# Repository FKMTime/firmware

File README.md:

# FKMTime firmware

## Main Pinout

| #   | IO#   | ADC/STRAP/USB | USAGE          | Notes                  |
|-----|-------|---------------|----------------|------------------------|
| 0   | IO4   | ADC           | SPI SCK        |                        |
| 1   | IO5   | ADC           | SPI MISO       |                        |
| 2   | IO6   |               | SPI MOSI       |                        |
| 3   | IO7   |               |                |                        |
| 4   | IO8   | STRAP         |                |                        |
| 5   | IO9   | STRAP / IPU   |                | INTERNAL PULLUP (10kOhm) |
| 6   | IO10  |               | SHIFTER DATA   |                        |
| 7   | RXD/IO20|             | JACK INPUT     |                        |
| 8   | TXD/IO21|             | SHIFTER CLK    |                        |
| 9   | IO18  | USB           | USB D-         |                        |
| 10  | IO19  | USB           | USB D+         |                        |
| 11  | IO3   | ADC           | BUTTON INPUT   |                        |
| 12  | IO2   | ADC / STRAP   | BATTERY INPUT  |                        |
| 13  | IO1   | ADC           | SHIFTER LATCH  |                        |
| 14  | IO0   | ADC           |                |                        |

**Notes:**
* **STRAP:** Strapping pin
* **IPU:** Internal Pull-up (10kOhm).
* **USB:** Pins used for USB communication.

## Shifters Configuration

| SHIFTER # | USAGE          | BIT1    | BIT2    | BIT3    | BIT4    | BIT5    | BIT6    | BIT7    | BIT8    |
|-----------|----------------|---------|---------|---------|---------|---------|---------|---------|---------|
| 0         | BUTTONS MATRIX | BTN1    | BTN2    | BTN3    | BTN4    |         |         |         |         |
| 1         | LCD 16x2       | SPI_CS  | BL      | RS      | E       | D7      | D6      | D5      | D4      |
| 2         | DISPLAY DIGIT1 | TODO    | TODO    | TODO    | TODO    | TODO    | TODO    | TODO    | TODO    |
| 3         | DISPLAY DIGIT2 | TODO    | TODO    | TODO    | TODO    | TODO    | TODO    | TODO    | TODO    |
| 4         | DISPLAY DIGIT3 | TODO    | TODO    | TODO    | TODO    | TODO    | TODO    | TODO    | TODO    |
| 5         | DISPLAY DIGIT4 | TODO    | TODO    | TODO    | TODO    | TODO    | TODO    | TODO    | TODO    |
| 6         | DISPLAY DIGIT5 | TODO    | TODO    | TODO    | TODO    | TODO    | TODO    | TODO    | TODO    |
| 7         | DISPLAY DIGIT6 | TODO    | TODO    | TODO    | TODO    | TODO    | TODO    | TODO    | TODO    |

## PCB
Pcb files are available as easyeda pro project.
File `FKM3.epro`

## 3D design 
You can view it and/or export it on onshape: 
 - [v1](https://cad.onshape.com/documents/a197fb44982d02cf4b905a34/w/d4d582c400841c8d2afd5356/e/063a9ed468737fb6f67b27f0?renderMode=0&uiState=65d2904a62856512eae60b89)
 - [v2](https://cad.onshape.com/documents/b9e6ecc4d8625f5993c3f9f8/w/500dd0485ca5c8c194e3d3fd/e/a40639e650796ab94408e0d7?renderMode=0&uiState=66239c4fa9b8ad7b949dae01)

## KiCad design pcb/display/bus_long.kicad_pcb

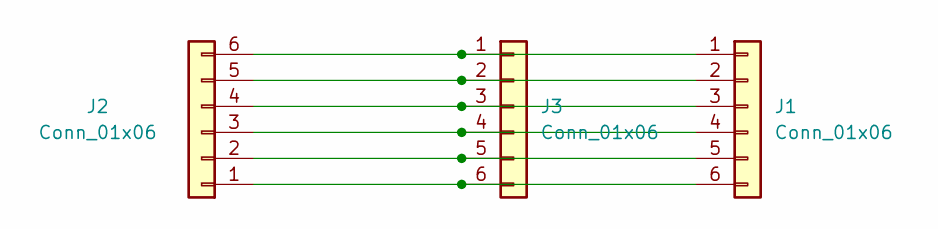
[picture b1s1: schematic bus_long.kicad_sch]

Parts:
J1, J2, J3: Conn_01x06; PinHeader_1x06_P2.54mm_Vertical

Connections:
unnamed: J1.1, J2.6, J3.1
unnamed: J1.2, J2.5, J3.2
unnamed: J1.3, J2.4, J3.3
unnamed: J1.4, J2.3, J3.4
unnamed: J1.5, J2.2, J3.5
unnamed: J1.6, J2.1, J3.6

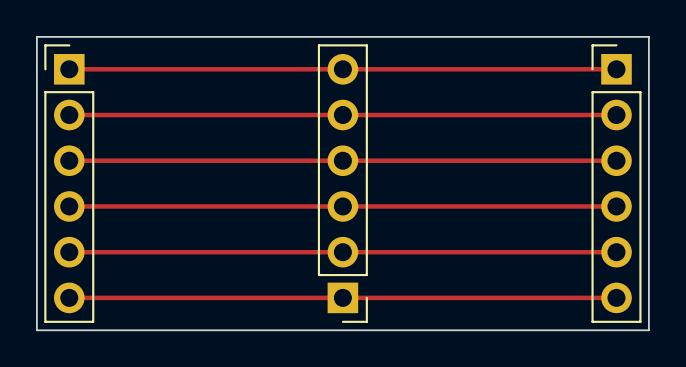
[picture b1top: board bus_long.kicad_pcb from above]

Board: 2 copper layers, 34.0 x 16.3 mm, 3 parts (0 on the bottom side), 6 nets.

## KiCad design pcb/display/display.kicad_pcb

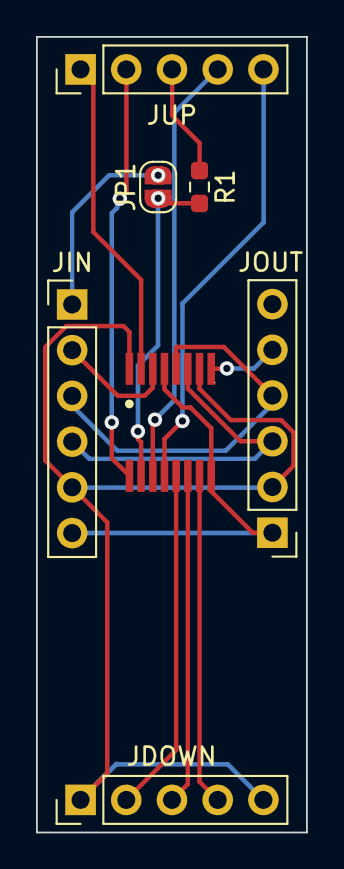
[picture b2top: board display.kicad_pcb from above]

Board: 2 copper layers, 15.0 x 44.2 mm, 7 parts (0 on the bottom side), 16 nets.

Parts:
JDOWN: DOWN; PinHeader_1x05_P2.54mm_Vertical
JIN: INPUT; PinHeader_1x06_P2.54mm_Vertical
JOUT: OUTPUT; PinHeader_1x06_P2.54mm_Vertical
JP1: SolderJumper_2_Open; SolderJumper-2_P1.3mm_Open_RoundedPad1.0x1.5mm
JUP: UP; PinHeader_1x05_P2.54mm_Vertical
R1: R220; R_0603_1608Metric_Pad0.98x0.95mm_HandSolder
U1: 74HC595; TSSOP16

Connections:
8_O: JIN.1, JP1.2 (B)
+5V: JDOWN.1, JDOWN.5, JIN.5, JOUT.2, U1.10 (~SRCLR), U1.16 (VCC)
DS: JIN.2, U1.14 (SER)
DS_O: JOUT.5, U1.9 (QH')
GND: JIN.6, JOUT.1, U1.8 (GND), U1.13 (~OE)
unnamed: JUP.3, R1.1
QA: JUP.1, U1.15 (QA)
QB: JUP.2, U1.1 (QB)
QC: JP1.1 (A), R1.2, U1.2 (QC)
QD: JUP.4, U1.3 (QD)
QE: JUP.5, U1.4 (QE)
QF: JDOWN.2, U1.5 (QF)
QG: JDOWN.3, U1.6 (QG)
QH: JDOWN.4, U1.7 (QH)
SHCP: JIN.4, JOUT.3, U1.11 (SRCLK)
STCP: JIN.3, JOUT.4, U1.12 (RCLK)

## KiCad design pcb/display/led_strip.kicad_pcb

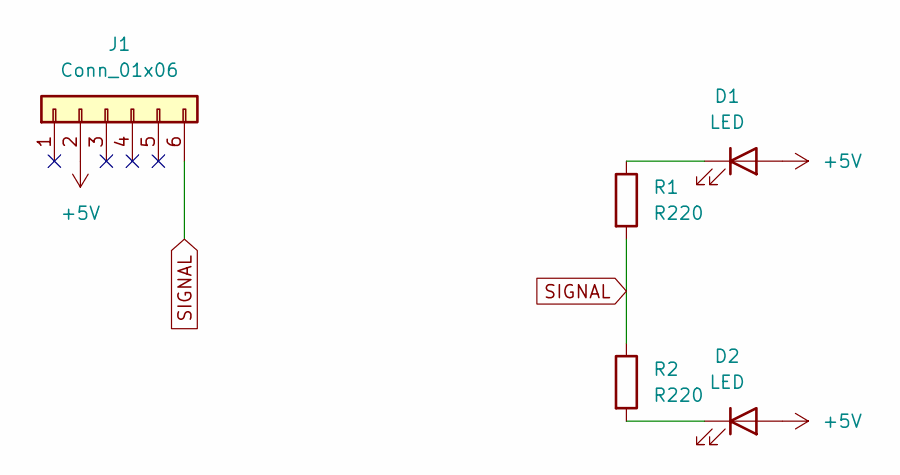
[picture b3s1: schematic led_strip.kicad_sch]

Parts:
D1, D2: LED; LED_D3.0mm
J1: Conn_01x06; PinHeader_1x06_P2.54mm_Vertical
R1, R2: R220; R_0603_1608Metric_Pad0.98x0.95mm_HandSolder

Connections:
+5V: D1.2 (A), D2.2 (A), J1.2
unnamed: D1.1 (K), R1.1
unnamed: D2.1 (K), R2.2
SIGNAL: J1.6, R1.2, R2.1

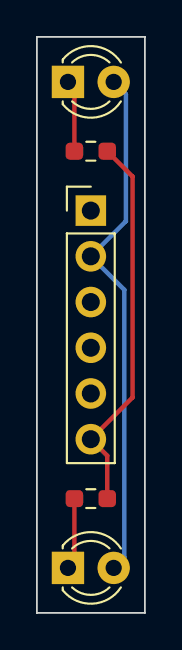
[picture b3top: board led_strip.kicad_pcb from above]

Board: 2 copper layers, 6.0 x 32.0 mm, 5 parts (0 on the bottom side), 4 nets.

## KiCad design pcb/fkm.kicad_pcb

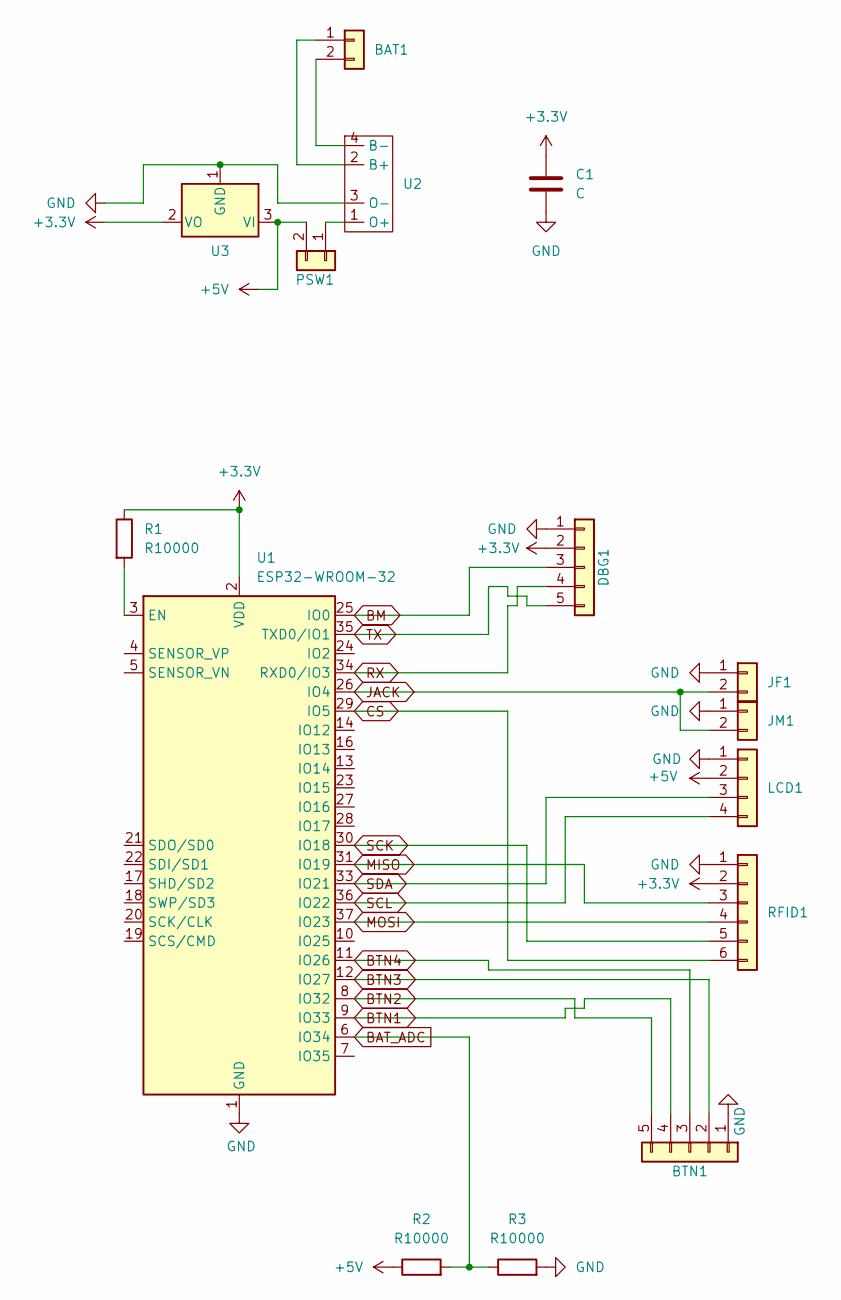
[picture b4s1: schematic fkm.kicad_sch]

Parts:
BAT1: BAT1; PinHeader_1x02_P2.54mm_Vertical
BTN1: Conn_01x05; PinHeader_1x05_P2.54mm_Vertical
C1: C; C_0805_2012Metric_Pad1.18x1.45mm_HandSolder
DBG1: Conn_01x05; PinHeader_1x05_P2.00mm_Vertical
JF1: JACK_FEMALE; PinHeader_1x02_P2.54mm_Vertical
JM1: JACK_MALE; PinHeader_1x02_P2.54mm_Vertical
LCD1: LCD; PinHeader_1x04_P2.54mm_Vertical
PSW1: POWER_SW; PinHeader_1x02_P2.54mm_Vertical
R1, R2, R3: R10000; R_0805_2012Metric_Pad1.20x1.40mm_HandSolder
RFID1: RFID; PinHeader_1x06_P2.54mm_Vertical
U1: ESP32-WROOM-32
U2: 18650; 18650usbc
U3: AMS1117-3.3; SOT-223-3_TabPin2

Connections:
+3.3V: C1.2, DBG1.2, R1.1, RFID1.2, U1.2 (VDD), U3.2 (VO)
+5V: LCD1.2, PSW1.2, R2.1, U3.3 (VI)
BAT_ADC: R2.2, R3.1, U1.6 (IO34)
BM: DBG1.3, U1.25 (IO0)
BTN1: BTN1.4, U1.9 (IO33)
BTN2: BTN1.5, U1.8 (IO32)
BTN3: BTN1.2, U1.12 (IO27)
CS: RFID1.6, U1.29 (IO5)
GND: BTN1.1, C1.1, DBG1.1, JF1.1, JM1.1, LCD1.1, R3.2, RFID1.1, U1.1 (GND), U1.15 (GND), U1.38 (GND), U1.39 (GND), U2.3 (O-), U3.1 (GND)
JACK: JF1.2, JM1.2, U1.26 (IO4)
MISO: RFID1.3, U1.31 (IO19)
MOSI: RFID1.4, U1.37 (IO23)
unnamed: BAT1.1, U2.2 (B+)
unnamed: BAT1.2, U2.4 (B-)
unnamed: BTN1.3, U1.11 (IO26)
unnamed: PSW1.1, U2.1 (O+)
unnamed: R1.2, U1.3 (EN)
RX: DBG1.4, U1.34 (RXD0/IO3)
SCK: RFID1.5, U1.30 (IO18)
SCL: LCD1.4, U1.36 (IO22)
SDA: LCD1.3, U1.33 (IO21)
TX: DBG1.5, U1.35 (TXD0/IO1)

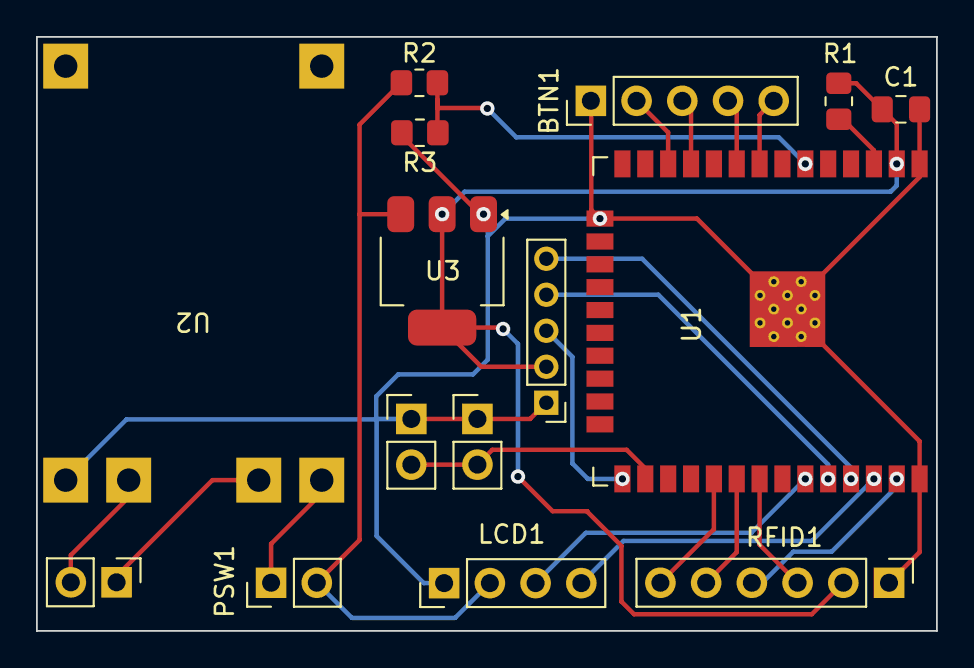
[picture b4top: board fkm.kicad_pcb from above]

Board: 2 copper layers, 50.0 x 33.0 mm, 15 parts (0 on the bottom side), 22 nets.

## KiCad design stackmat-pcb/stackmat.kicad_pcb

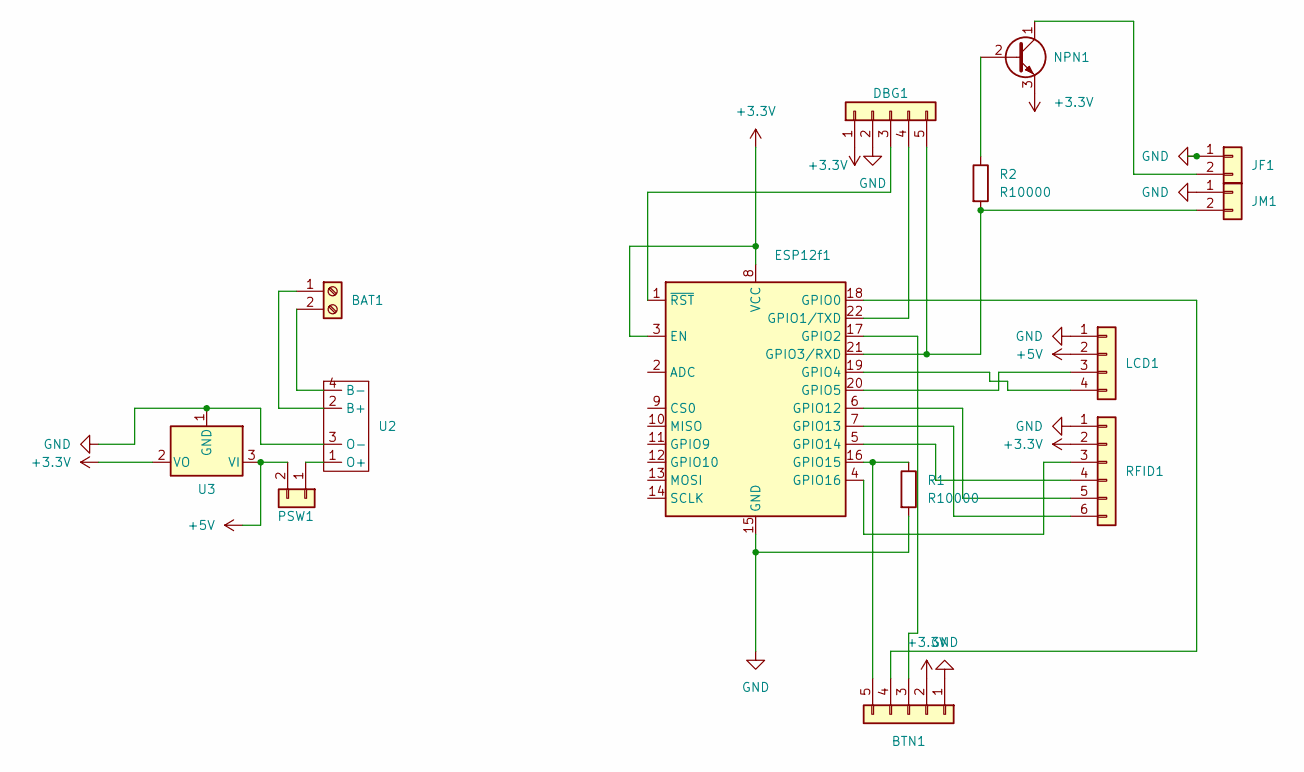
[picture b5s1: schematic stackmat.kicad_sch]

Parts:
BAT1: Screw_Terminal_01x02; TerminalBlock_4Ucon_1x02_P3.50mm_Horizontal
BTN1: Conn_01x05; PinHeader_1x05_P2.54mm_Vertical
DBG1: Conn_01x05; PinHeader_1x05_P2.54mm_Vertical
ESP12f1: ESP-12F/E; ESP-12E
JF1: JACK_FEMALE; PinHeader_1x02_P2.54mm_Vertical
JM1: JACK_MALE; PinHeader_1x02_P2.54mm_Vertical
LCD1: LCD; PinHeader_1x04_P2.54mm_Vertical
NPN1: BC337; TO-92_Inline
PSW1: POWER_SW; PinHeader_1x02_P2.54mm_Vertical
R1, R2: R10000; R_Axial_DIN0204_L3.6mm_D1.6mm_P7.62mm_Horizontal
RFID1: RFID; PinHeader_1x06_P2.54mm_Vertical
U2: 18650; 18650usbc
U3: AMS1117-3.3; SOT-223-3_TabPin2

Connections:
+3.3V: BTN1.2, DBG1.1, ESP12f1.3 (EN), ESP12f1.8 (VCC), NPN1.3 (E), RFID1.2, U3.2 (VO)
+5V: LCD1.2, PSW1.2, U3.3 (VI)
GND: BTN1.1, DBG1.2, ESP12f1.15 (GND), JF1.1, JM1.1, LCD1.1, R1.2, RFID1.1, U2.3 (O-), U3.1 (GND)
unnamed: BAT1.1, U2.2 (B+)
unnamed: BAT1.2, U2.4 (B-)
unnamed: BTN1.3, ESP12f1.17 (GPIO2)
unnamed: BTN1.4, ESP12f1.18 (GPIO0)
unnamed: BTN1.5, ESP12f1.16 (GPIO15), R1.1
unnamed: DBG1.3, ESP12f1.1 (~RST)
unnamed: DBG1.4, ESP12f1.22 (GPIO1/TXD)
unnamed: DBG1.5, ESP12f1.21 (GPIO3/RXD), JM1.2, R2.2
unnamed: ESP12f1.19 (GPIO4), LCD1.4
unnamed: ESP12f1.20 (GPIO5), LCD1.3
unnamed: ESP12f1.6 (GPIO12), RFID1.5
unnamed: ESP12f1.7 (GPIO13), RFID1.6
unnamed: ESP12f1.5 (GPIO14), RFID1.4
unnamed: ESP12f1.4 (GPIO16), RFID1.3
unnamed: JF1.2, NPN1.1 (C)
unnamed: NPN1.2 (B), R2.1
unnamed: PSW1.1, U2.1 (O+)

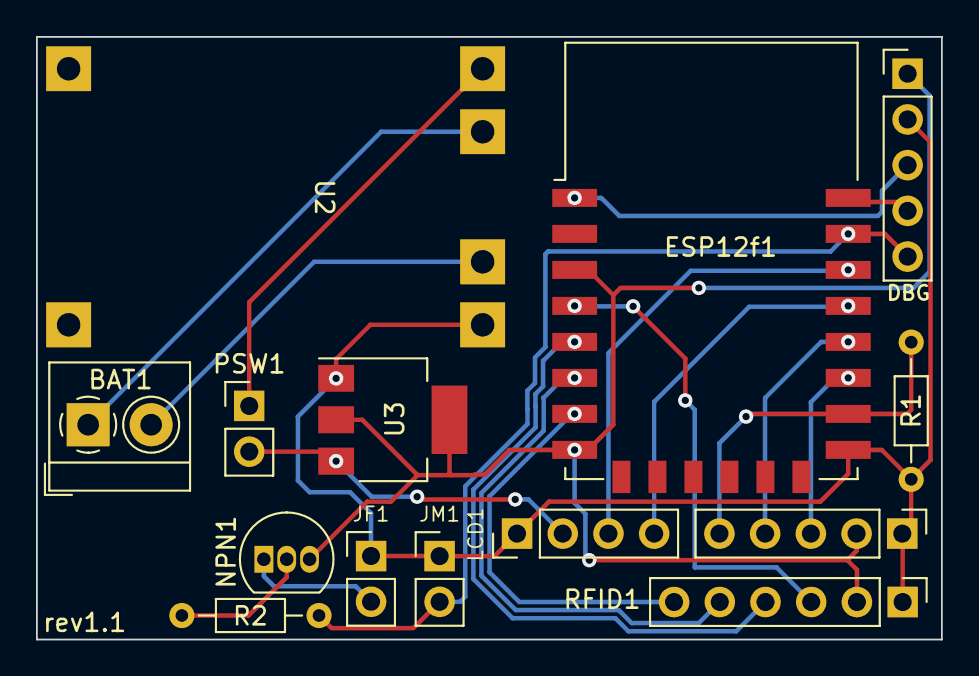
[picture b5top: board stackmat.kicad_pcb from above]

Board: 2 copper layers, 50.3 x 33.5 mm, 14 parts (0 on the bottom side), 20 nets.

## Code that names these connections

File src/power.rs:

//! Sleep state machine: Awake → Sleeping (radio off) → DeepSleep (chip off, button wakes it).
//!
//! Display/input code only calls [`request_sleep`] / [`wake`] / [`enter_deep_sleep`];
//! [`Supervisor::tick`] (main loop) does the radio, websocket and BLE side of each transition.

use embassy_sync::{blocking_mutex::raw::CriticalSectionRawMutex, signal::Signal};
use embassy_time::{Duration, Instant};
use esp_hal_wifimanager::WifiManager;
use portable_atomic::{AtomicBool, Ordering};

pub type SleepSignal = Signal<CriticalSectionRawMutex, bool>;

/// Time between the websocket close frame and the radio going off; also debounces quick wakes.
const SLEEP_SETTLE: Duration = Duration::from_secs(15);

static SLEEPING: AtomicBool = AtomicBool::new(false);
/// v3 only: the cpu runs at 10 MHz until the next reset.
static DEEPER: AtomicBool = AtomicBool::new(false);

pub fn is_sleeping() -> bool {
    SLEEPING.load(Ordering::Relaxed)
}

#[cfg_attr(not(feature = "v3"), allow(dead_code))]
pub fn is_deeper_sleeping() -> bool {
    DEEPER.load(Ordering::Relaxed)
}

pub fn request_sleep() {
    SLEEPING.store(true, Ordering::Relaxed);
}

pub fn wake() {
    SLEEPING.store(false, Ordering::Relaxed);
}

/// Powers the chip down until one of the four buttons is pressed (wake = reset).
#[cfg(feature = "v4")]
pub fn enter_deep_sleep() -> ! {
    use esp_hal::gpio::{Event, Input, InputConfig, Pin, Pull, WakeupConfig};
    use esp_hal::rtc_cntl::sleep::{LowPower, RtcSleepConfig};

    // SAFETY: called right before deep sleep, after which nothing else uses these pins.
    let (pins, lpwr) = unsafe {
        (
            [
                esp_hal::peripherals::GPIO0::steal().degrade(),
                esp_hal::peripherals::GPIO1::steal().degrade(),
                esp_hal::peripherals::GPIO2::steal().degrade(),
                esp_hal::peripherals::GPIO3::steal().degrade(),
            ],
            esp_hal::peripherals::LPWR::steal(),
        )
    };

    // pull-down like the old RtcioWakeupSource did for a high-level wake
    let input_config = InputConfig::default().with_pull(Pull::Down);
    let wakeup_config = WakeupConfig::default().with_low_power_path(true);
    let mut wakeup_pins = pins.map(|pin| Input::new(pin, input_config));
    for pin in &mut wakeup_pins {
        if let Err(e) = pin.apply_wakeup_config(&wakeup_config) {
            log::error!("Wakeup pin config failed: {e:?}");
        }
        pin.listen(Event::HighLevel);
    }

    LowPower::new(lpwr).sleep_deep(RtcSleepConfig::deep())
}

/// v3 has no wakeable deep sleep: the cpu clock drops to 10 MHz until the next reset.
#[cfg(feature = "v3")]
pub fn enter_deep_sleep() {
    crate::utils::deeper_sleep();
    DEEPER.store(true, Ordering::Relaxed);
}

/// Applies sleep transitions to the radio, websocket and BLE tasks.
pub struct Supervisor<'a> {
    wifi: &'a WifiManager,
    sleeping: bool,
    /// Set while waiting [`SLEEP_SETTLE`] before turning the radio off.
    settling_since: Option<Instant>,
}

impl<'a> Supervisor<'a> {
    pub fn new(wifi: &'a WifiManager) -> Self {
        Self {
            wifi,
            sleeping: false,
            settling_since: None,
        }
    }

    /// Call periodically (never blocks for long).
    pub fn tick(&mut self) {
        let sleeping = is_sleeping();

        if let Some(since) = self.settling_since {
            if !sleeping {
                // woken while settling: reset the ws state, the next tick restarts everything
                self.settling_since = None;
                crate::ws::SLEEP.signal(true);
            } else if since.elapsed() >= SLEEP_SETTLE {
                self.settling_since = None;
                crate::ws::SLEEP.signal(true);
                self.wifi.stop_radio();
            }
            return;
        }

        if sleeping == self.sleeping {
            return;
        }

        self.sleeping = sleeping;
        crate::bluetooth::SLEEP.signal(sleeping);
        if sleeping {
            log::warn!("Entering sleep mode!");
            crate::ws::close(4000, "Going into sleep mode");
            self.settling_since = Some(Instant::now());
        } else {
            crate::ws::SLEEP.signal(false);
            self.wifi.restart_radio();
        }
    }
}

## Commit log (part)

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2025-03-13 feat: qa tests
2025-03-13 feat: add wifi setup to qa tests
2025-03-23 chore: update dependencies
2025-03-28 feat: do not use nvs if in qa
2025-03-29 chore: print firmware/version/revision on startup
2025-03-29 feat: add Auto Server Discovery checkbox to wifi panel
2025-03-31 chore: print button presses on qa mode
2025-04-05 fix: speed up cpu clock
2025-04-05 fix: multiple things
2025-04-06 chore: sleep feature (to enable/disable sleep)
2025-04-06 feat: use ag-lcd fork with async support fix: decrease button debounce time fix: ms time to str above 9 minutes 59seconds
2025-04-08 chore: print card skip warn msg
2025-04-08 fix: do not try to send frame if its too big
2025-04-08 feat: frame splitting
2025-04-09 feat: check heap space on log
2025-04-10 chore: mkdir /tmp/fkm-build in release script
2025-04-13 chore: new version of easyeda pcb proj
2025-04-15 explore: esp-now communication
2025-05-15 fix: clippy warnings
2025-05-15 fix: uart slowdown issue (closes #21 #22)
2025-05-15 fix: release build const
2025-05-29 chore: update dependencies (so it will build)
2025-05-29 fix: clippy error
2025-05-29 docs: add pinout map to readme
2025-06-03 chore: update to newer version of esp-hal
2025-06-03 fix: fmt
2025-06-24 feat: use async interface for battery adc readings (esp32c3 only)
2025-06-25 chore: remove esp32 generic port with cleanup
2025-06-25 fix: build/clippy ci with removed `esp32c3` feature
2025-06-25 fix: actually fix ci
2025-07-16 chore: update to newest esp-hal
2025-07-16 fix: fmt issues
2025-07-17 chore: use reeleased version of esp-hal-wifimanager (finally!)
2025-07-18 feat: better startup screen
2025-08-07 feat: update pcb proj
2025-08-17 chore: update mfrc crate
2025-09-09 chore: dependencies bump
2025-09-22 feat: auto add device feature fix: show proper ws_rw errors
2025-09-23 fix: typo
2025-09-24 feat: generate sign key
2025-09-24 feat: packet signing
2025-09-25 explore: check secured read from rfid card [skip ci]
2025-09-25 fix: invalidate SIGN_KEY on reset wifi
2025-09-26 fix: self signed rsa certs
2025-09-27 feat: server trust
2025-09-27 explore: test rfid read/write secured
2025-09-28 fix: tls read select cancel
2025-09-28 feat: recv fkm_token from device settings
2025-10-01 feat: secured rfid check
2025-10-03 fix: return from ws_rw loop on error (closes #25)
2025-10-03 feat: only update when server is trusted
2025-10-06 explore: disable usb after wifi connection
2025-10-11 fix: do not print token in the info log (use debug)
2025-10-12 wip: bluetooth connection to the own displays
2025-10-13 chore: update esp-hal version
2025-10-14 fix: update wifimanager to fix "sticky" ble
2025-10-14 wip: config menu
2025-10-14 wip: signing and unsigning cards
2025-10-14 wip: card signing UI
2025-10-15 wip: try to connect to fkm display example [skip ci]
2025-10-15 explore: send bt data constantly [skip ci]
2025-10-15 explore: detect disconnect from peer [skip ci]
2025-10-16 wip: messy ble display re-bonding [skip ci]
2025-10-17 wip: better menu scene management [skip ci]
2025-10-18 wip: ble displays menu [skip ci]
2025-10-18 wip: connect to ble from menu [skip ci]
2025-10-19 feat: better ble display connection management
2025-10-19 fix: ble connection
2025-10-19 chore: make ble signalling cleaner
2025-10-20 chore: more error handling (no unwraps, only expects in codepath's that cannot fail)
2025-10-20 chore: even less expect's
2025-10-21 feat: only allow cards signing/unsigning when auto setup enabled
2025-10-23 feat: ble display sleep
2025-10-30 feat: show server not trusted error after connection
2025-10-30 chore: expect is no more
2025-10-31 chore: update to stable version of esp-hal
2025-10-31 chore: remove old esp-now experiment
2025-11-01 fix: lcd hanging on start (fucking wifi is blocking - not my issue)
2025-11-02 feat: different battery curves
2025-11-02 feat: change battery sample rate after lcd display
2025-11-02 chore: change lower cutoff voltage (battery curve)
2025-11-19 chore: add clippy rule for unwraps, expects and panics
2025-12-02 chore: change mdns query
2026-01-10 fix: embedded-tls read cancel-safety
2026-01-11 fix: show autosetup disabled message when its disabled
2026-01-12 feat: add is_competitor field
2026-01-13 fix: rebuilding when nothing changed
2026-01-22 wip: new wifimanager release with different nvs
2026-02-09 wip: enter solve attempt message
2026-02-09 wip: temp disable server trust
2026-02-10 fix: saved state key length
2026-02-13 fix: esp32c3 deeper sleep
2026-02-13 fix: skip card processing when server isn't connected (closes #28)
2026-02-13 fix: sleep set server_connected to false
2026-02-13 fix: FRAME_CHANNEL deadlock
2026-02-13 fix: do not soft power down rfid module on sleep
2026-02-15 feat: update wifimanager and enable ota feature
2026-02-24 fix: elliptic-curve build
2026-02-24 fix: rfid in qa mode
2026-02-24 fix: build script for github release builds
2026-02-26 feat: show wifi connection lost on screen
2026-02-26 fix: clippy warning
2026-02-26 chore: reset connection lost flag after server connection
2026-02-26 feat: use new esp-hal-wifimanager that sets dhcp hostname
2026-03-09 wip: v4 firmware [SKIP CI]
2026-03-09 wip: shared i2c struct with embedded_hal_async [SKIP CI]
2026-03-09 wip: async oled driver [SKIP CI]
2026-03-09 wip: lcd in own task
2026-03-09 wip: bq27441 gauage module
2026-03-09 wip: ported everything (messy as fuck, everything is to change)
2026-03-09 wip: store oled framebuffer in heap memory
2026-03-11 wip: v4 feature
2026-03-11 wip: working? v3 feature
2026-03-11 fix: ci features flags for clippy
2026-03-11 wip: test claude generated icons on top bar
2026-03-12 wip: test layout with pixelart generator
2026-03-12 feat: battery update oled state
2026-03-12 feat: show status icons on top bar
2026-03-12 fix: solve time not displayed when the same as last solve time
2026-03-12 wip: implement more oled stuff
2026-03-12 feat: proper startup screen
2026-03-12 wip: timer scene
2026-03-13 feat: slightly cleanup layouts code
2026-03-13 feat: implement config menus
2026-03-13 feat: implement the rest of oled display code
2026-03-13 explore: better deep sleep
2026-03-15 feat: enable rfid soft power down
2026-03-15 chore: remove avg current battery consumption during sleep
2026-03-18 chore: log parsed saved state
2026-03-19 feat: add debug power loss, sleep wakeup's prints
2026-03-19 feat: text wrap
2026-03-19 feat: better scollable config menus
2026-03-19 fix: delegate call translation
2026-03-19 fix: sleep timer reset when battery percentage changes
2026-03-20 chore: update release script for v3 and v4
2026-03-20 fix: last_solve_time in signaled global state
2026-03-21 fix: e2e build
2026-03-21 fix: v4 inspection time display on finished scene
2026-03-21 feat: send current timer time alongside logs
2026-03-21 feat: translation of inspection key
2026-04-15 feat: update wifi panel
2026-04-17 feat(v4): add buzzer and rotate lcd
2026-04-17 feat(v4): rfid buzzer volume controls
2026-04-18 wip: esp-hal 1.1.0 port
2026-04-18 fix: update wifimanager to use fork esp-nvs
2026-04-19 fix: unwraps and expects
2026-04-19 feat: init websocket and tls buffers into dram2 (no heap alloc)
2026-04-19 fix: own sleep power consumption (stop wifi controller)
2026-04-19 fix: center sleep text to the screen not to main rect
2026-04-22 feat: send logs over binary channel (instead of json text)
2026-04-22 wip: qr codes!
2026-04-22 feat: change backtrace store data chore: make all nvs keys as consts
2026-04-22 wip: error log [skip ci]
2026-04-22 feat: add version to error log stacktrace
2026-04-22 feat: save current version in backtrace bytes
2026-04-22 Add error log submenu state and interaction flow
    Agent-Logs-Url: https://github.com/FKMTime/firmware/sessions/c858a510-9b6d-44c7-a6f1-dffbab89ae2c
2026-04-22 Implement v3/v4 error log submenu UI and flow
    Agent-Logs-Url: https://github.com/FKMTime/firmware/sessions/c858a510-9b6d-44c7-a6f1-dffbab89ae2c
2026-04-22 Changes before error encountered
    Agent-Logs-Url: https://github.com/FKMTime/firmware/sessions/89d3fa84-427f-4508-8f14-dc7847c63c14
2026-04-23 fix: add draw_scrollable_details_text, remove auto-scroll, add left/right scroll for error log details
    Agent-Logs-Url: https://github.com/FKMTime/firmware/sessions/fa53653d-eca7-4b98-bb2c-499a5ae266b5
2026-04-23 refactor: use shared DETAILS_VISIBLE_LINES const, fix unused variable
    Agent-Logs-Url: https://github.com/FKMTime/firmware/sessions/fa53653d-eca7-4b98-bb2c-499a5ae266b5
2026-04-23 fix: print all stacktrace addrs, remove +N more truncation
    Agent-Logs-Url: https://github.com/FKMTime/firmware/sessions/6c60fb5d-e1eb-4a4b-92c5-48ef2d1b0652
2026-04-23 faet: qr codes with actual data
2026-04-23 feat: store crash timestamp in flash backtrace and use it in error log
    Agent-Logs-Url: https://github.com/FKMTime/firmware/sessions/8285feb3-34f9-46a8-9099-6fbe67030068
2026-04-23 fix: clippy
2026-04-23 refactor: remove backwards compat from backtrace_store, single format only
    Agent-Logs-Url: https://github.com/FKMTime/firmware/sessions/ba311f6f-acb5-4f05-be53-e68e5edb0325
2026-04-23 feat: reduce binary size (minify panels)
2026-04-23 wip: test web flasher (with partitions table etc)
2026-04-27 feat: panic self recovery (wipe nvs)
2026-04-27 fix(v3): error log menu
2026-04-27 fix: do not send empty logs, do not delete stacktrace on self recovery
2026-04-27 fix: clippy errors
2026-04-28 wip: add error logs for most common issues
2026-04-29 feat: show critical error screen when partition table is wrong
2026-04-30 feat: update build scripts to build v3 and v4
2026-05-05 feat: actually upload boundled firmware files (elf etc)
2026-05-07 chore: auto upload merged dist bins to fkmdocs
2026-05-11 feat: disable buzzer when inspection is disabled
2026-05-11 feat(v4): display only penalty string when solve time is 0
2026-05-11 feat: show scan judge card error when competitor scanned for the second time
2026-05-12 fix: use sound enbaled device settings boolean
2026-05-14 feat: set device settings command
2026-05-15 feat: send close frame on sleep
2026-05-15 fix: sleep logic
2026-05-15 feat: dump crash log cmd
2026-05-15 chore: dump crash/error log from memory instead of nvs
2026-05-16 fix: update deps and do not optimize for size esp-hal package
2026-05-19 feat: add secondary text for groups (for v4 only)
2026-05-19 chore: update rust ci dependencies
2026-05-19 feat: limit solve time (closes #33) feat: interpolate time when timer conn lost (even after 10mins) (closes #32) chore: removed old v3 display connector support
2026-05-19 feat: set dnf when time clamped on limit
2026-05-20 wip: experimental timer functionality (stackmatless timer)
2026-05-20 fix: timer func stop
2026-05-20 wip: fix deadlocks
2026-05-20 fix: deadlocks when battery gauge fails to read
2026-05-20 fix: formatting
2026-05-20 feat: different dnf display on v4
2026-05-20 feat: only show 2 diits of ms
2026-05-22 explore: timer func with "real" pads
2026-05-29 fix: clear old display data buffer
2026-06-07 chore: update esp radio
